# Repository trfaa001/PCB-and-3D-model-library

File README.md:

# PCB and 3D model library
A portfolio of small PCB designs, schematics and 3D models that are too minor to justify having their own repository.

Click on any hyperlink to view images, renders and CAD files for specified item.

### PCB / Electrical Projects
- [DIP-8 breakout board](/PCB/Kicad/DIP8%20breakout/README.md) (soldering unfinished)
- [OV-imponator power circuit](/PCB/Kicad/imponatorPower/README.md)

### 3D design/printing projects
#### Related to sim racing
- [Motor table clamp](/3D/Fusion_360/Sim_racing_table_clamp/README.md)
- [Small monitor mount](/3D/Fusion_360/Small_screen_mount/README.md)
- [Motor shaft attachment for QR](/3D/Fusion_360/Motor_shaft_to_6_hole_pattern/README.md)

## Folder structure
- "/PCB/" - PCB project files, schematics
- "/3D/" - CAD files, renders

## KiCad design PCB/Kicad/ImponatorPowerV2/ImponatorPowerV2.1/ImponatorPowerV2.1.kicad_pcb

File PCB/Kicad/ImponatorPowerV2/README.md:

# OV-imponator power circuit

<!-- Project description -->
A small circuit able to charge two AA Li-Ion and Li-Po batteries with USB PD and deliver 5V power to an external device. From the previous designed I have added a LED matrix, 4 buttons, 1 microphone, 4 addresable LEDs and a sliding POT.meter connected to a Silicon Labs microcontroller.

I routed a 4 layer and a 6 layer PCB for this design, because the price for a 6 layer design was cheaper when I checked the price of ordering a 4 layer pcb with vias in pads.

## images
### PCB design
#### 4 layer PCB

#### 6 layer PCB

## Physical image

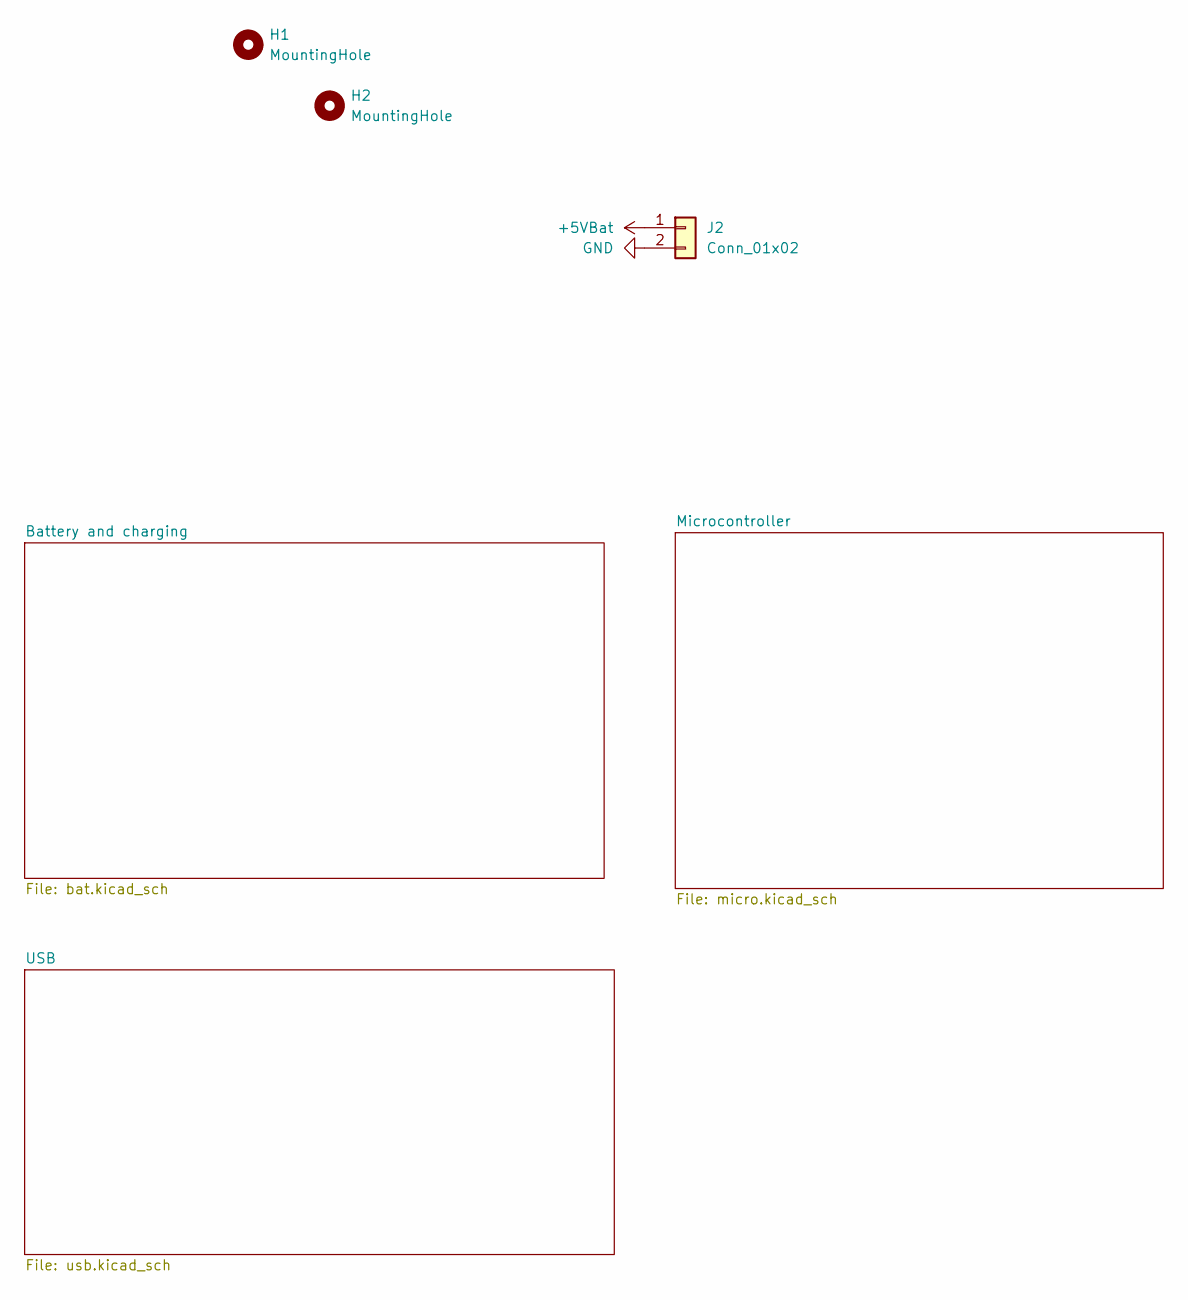
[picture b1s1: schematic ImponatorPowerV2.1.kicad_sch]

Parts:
H1, H2: MountingHole; MountingHole_2.2mm_M2
J2: Conn_01x02; JST_XH_S2B-XH-A_1x02_P2.50mm_Horizontal

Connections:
+5VBat: J2.1; also elsewhere on the board
GND: J2.2; also elsewhere on the board

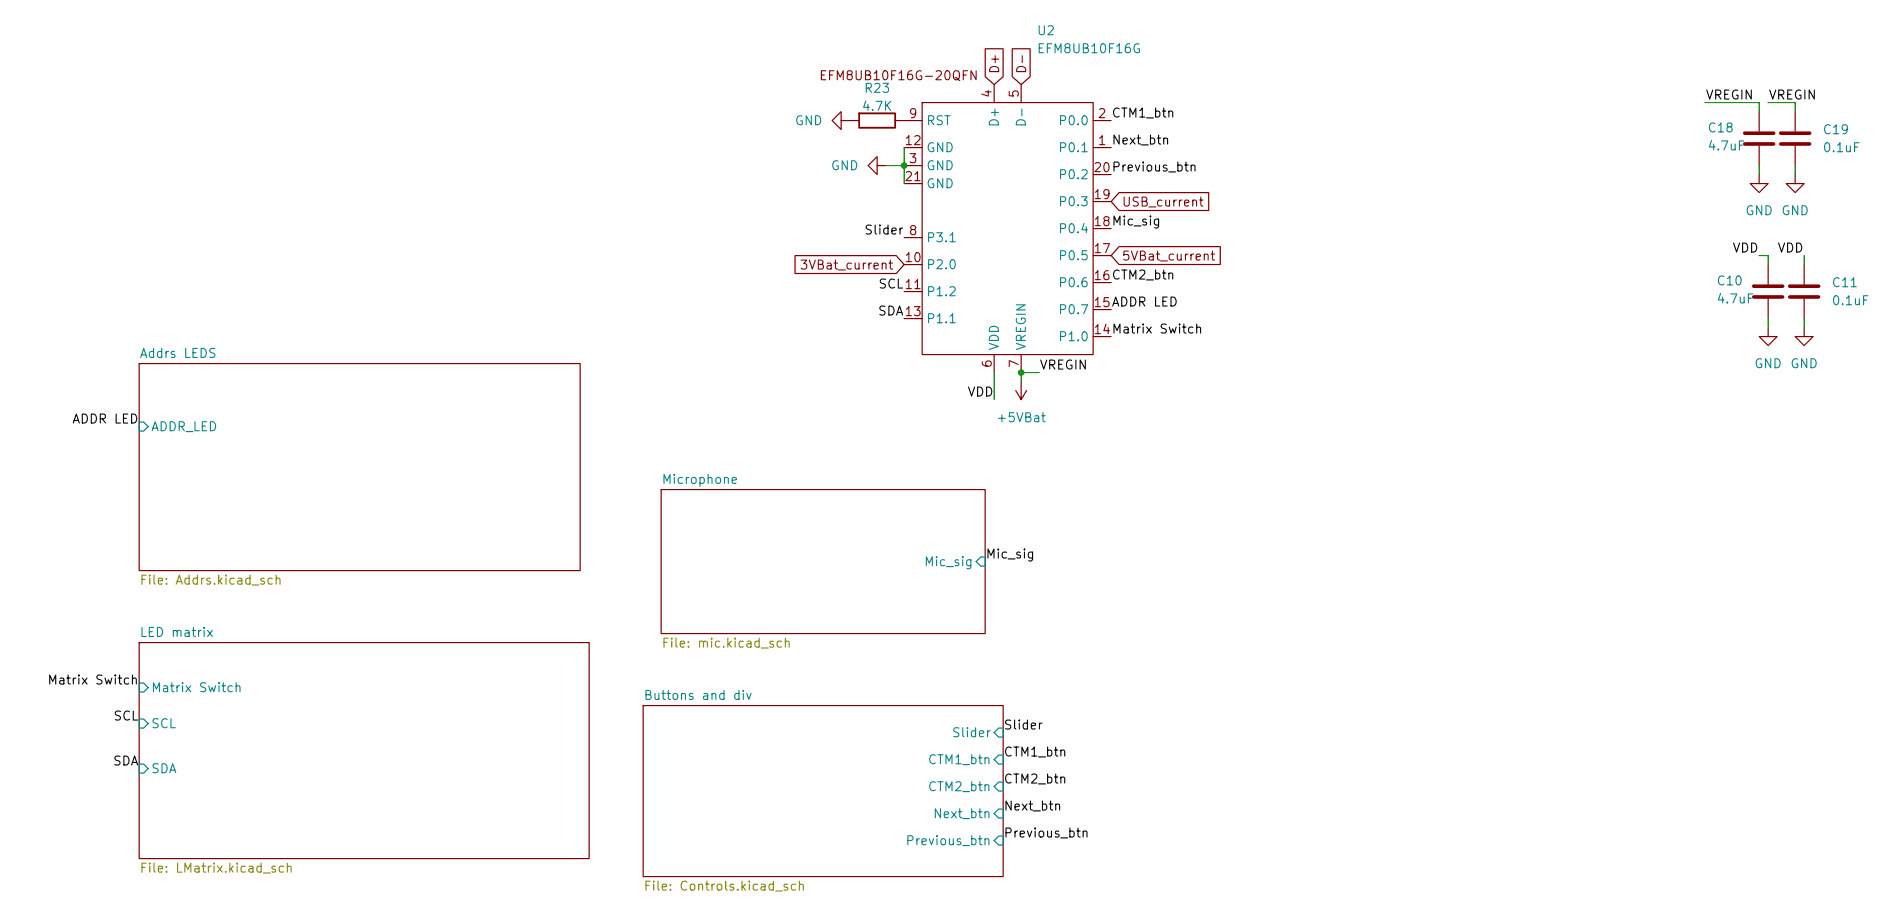
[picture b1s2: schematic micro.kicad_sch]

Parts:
C10, C18: 4.7uF; C_0805_2012Metric
C11, C19: 0.1uF; C_0805_2012Metric
R23: 4.7K; R_0603_1608Metric
U2: EFM8UB10F16G; QFN-20-1EP_3x3mm_P0.4mm_EP1.65x1.65mm

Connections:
3VBat_current: U2.10 (P2.0); also elsewhere on the board
5VBat_current: U2.17 (P0.5); also elsewhere on the board
+5VBat: C18.1, C19.1, U2.7 (VREGIN); also elsewhere on the board
/Microcontroller/ADDR LED: U2.15 (P0.7); also elsewhere on the board
/Microcontroller/CTM1_btn: U2.2 (P0.0); also elsewhere on the board
/Microcontroller/CTM2_btn: U2.16 (P0.6); also elsewhere on the board
/Microcontroller/Matrix Switch: U2.14 (P1.0); also elsewhere on the board
/Microcontroller/Mic_sig: U2.18 (P0.4); also elsewhere on the board
/Microcontroller/Next_btn: U2.1 (P0.1); also elsewhere on the board
/Microcontroller/Previous_btn: U2.20 (P0.2); also elsewhere on the board
/Microcontroller/SCL: U2.11 (P1.2); also elsewhere on the board
/Microcontroller/SDA: U2.13 (P1.1); also elsewhere on the board
/Microcontroller/Slider: U2.8 (P3.1); also elsewhere on the board
/Microcontroller/VDD: C10.1, C11.1, U2.6 (VDD)
D+: U2.4 (D+); also elsewhere on the board
D-: U2.5 (D-); also elsewhere on the board
GND: C10.2, C11.2, C18.2, C19.2, R23.2, U2.3 (GND), U2.12 (GND), U2.21 (GND); also elsewhere on the board
unnamed: R23.1, U2.9 (RST)
USB_current: U2.19 (P0.3); also elsewhere on the board

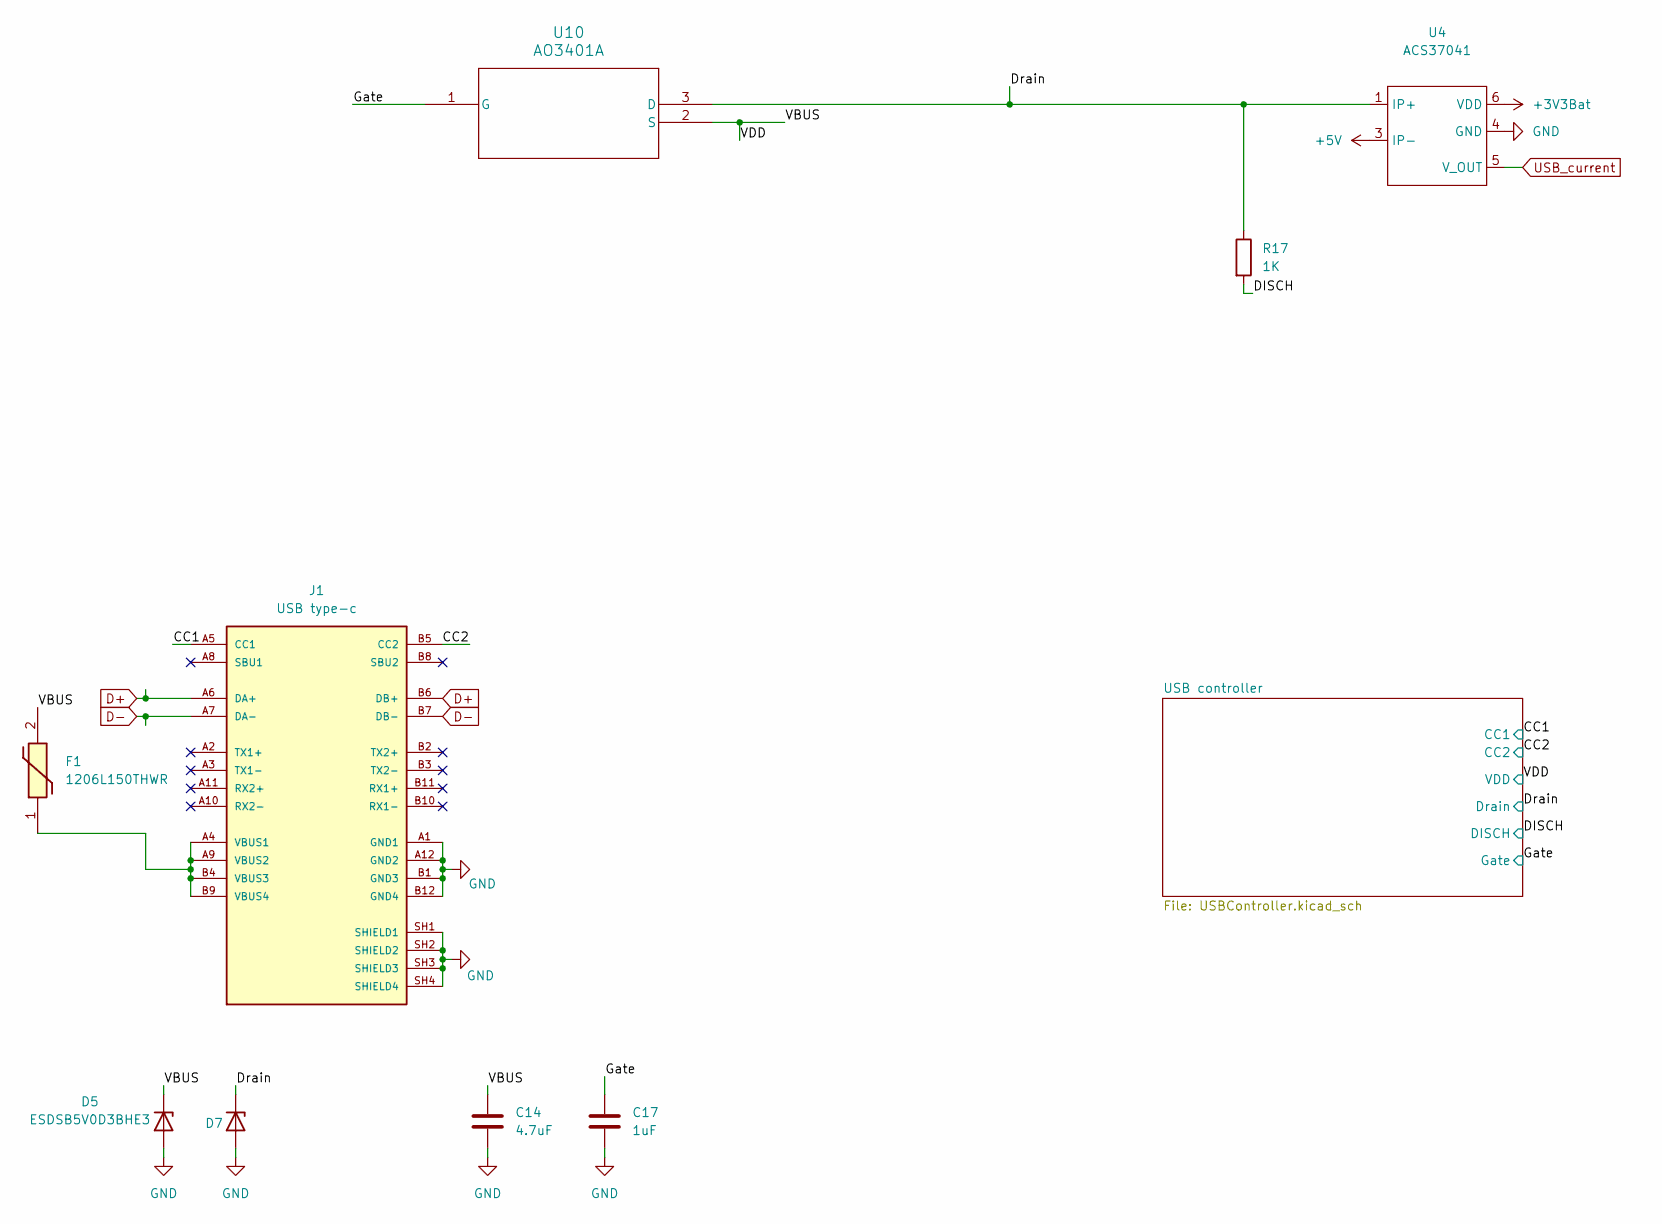
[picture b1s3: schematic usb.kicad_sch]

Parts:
C14: 4.7uF; C_0603_1608Metric
C17: 1uF; C_0603_1608Metric
D5, D7: ESDSB5V0D3BHE3; D_SOD-323
F1: 1206L150THWR; FUSC3216X100N; Manufacturer_Part_Number 1206L150THWR
J1: USB type-c; MOLEX_2024100002; PARTREV F1
R17: 1K; R_0603_1608Metric
U4: ACS37041; ACS37041KLHBLT-010B5
U10: AO3401A; SOT-23-3L_AOS

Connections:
+3V3Bat: U4.6 (VDD); also elsewhere on the board
+5V: U4.3 (IP-); also elsewhere on the board
/USB/CC1: J1.A5 (CC1); also elsewhere on the board
/USB/CC2: J1.B5 (CC2); also elsewhere on the board
/USB/DISCH: R17.2; also elsewhere on the board
/USB/Drain: D7.1 (K), R17.1, U4.1 (IP+), U10.3 (D); also elsewhere on the board
/USB/Gate: C17.1, U10.1 (G); also elsewhere on the board
/USB/VBUS: C14.1, D5.1 (K), F1.2, U10.2 (S); also elsewhere on the board
D+: J1.A6 (DA+), J1.B6 (DB+); also elsewhere on the board
D-: J1.A7 (DA-), J1.B7 (DB-); also elsewhere on the board
GND: C14.2, C17.2, D5.2 (A), D7.2 (A), J1.A1 (GND1), J1.A12 (GND2), J1.B1 (GND3), J1.B12 (GND4), J1.SH1 (SHIELD1), J1.SH2 (SHIELD2), J1.SH3 (SHIELD3), J1.SH4 (SHIELD4), U4.4 (GND); also elsewhere on the board
unnamed: F1.1, J1.A4 (VBUS1), J1.A9 (VBUS2), J1.B4 (VBUS3), J1.B9 (VBUS4)
USB_current: U4.5 (V_OUT); also elsewhere on the board

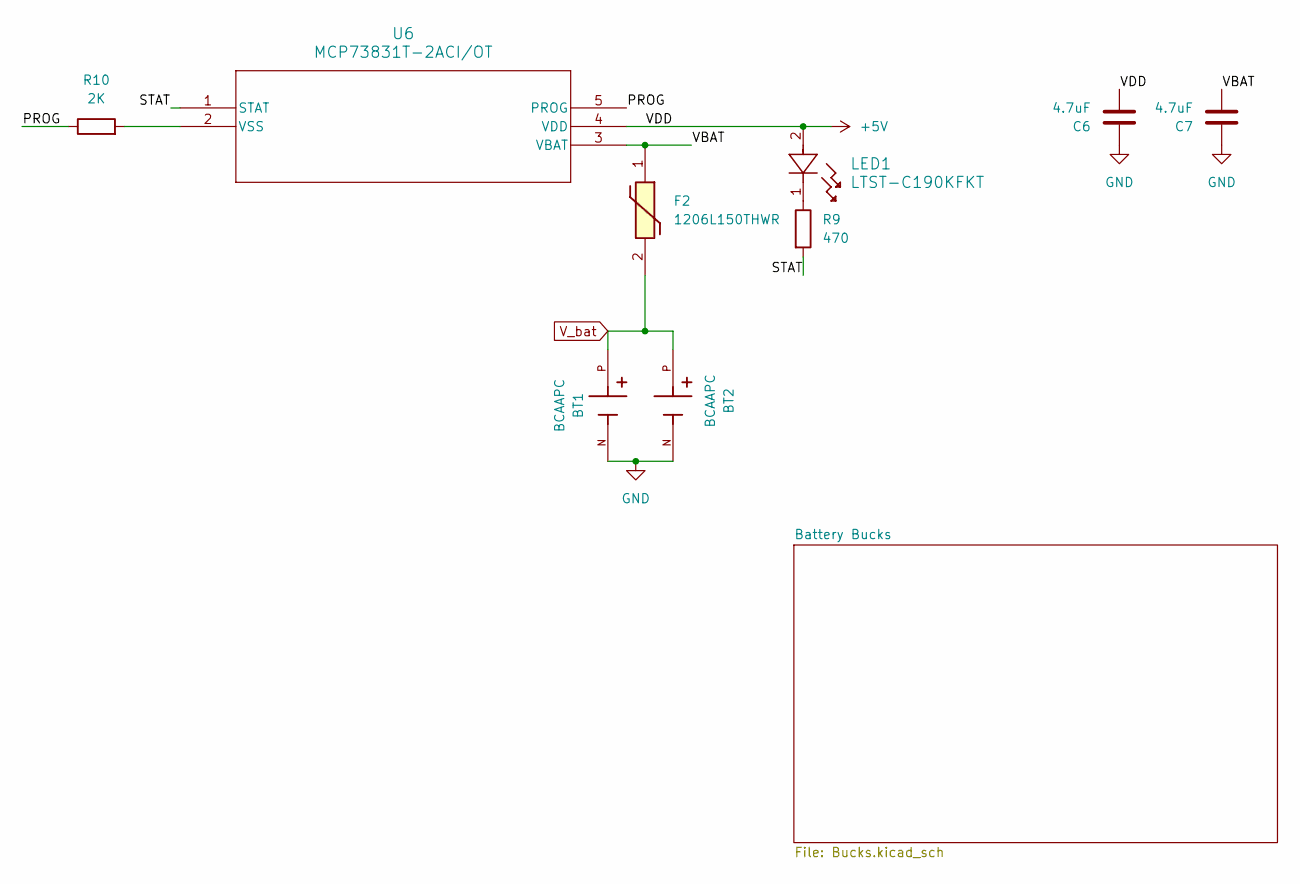
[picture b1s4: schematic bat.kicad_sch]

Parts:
BT1, BT2: BCAAPC; BAT_BCAAPC; PARTREV B
C6, C7: 4.7uF; C_0603_1608Metric
F2: 1206L150THWR; FUSC3216X100N; Manufacturer_Part_Number 1206L150THWR
LED1: LTST-C190KFKT; LED_LSTS-C190_LTO
R9: 470; R_0603_1608Metric
R10: 2K; R_0603_1608Metric
U6: MCP73831T-2ACI/OT; SOT-23-5

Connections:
+5V: C6.2, LED1.2, U6.4 (VDD); also elsewhere on the board
/Battery and charging/PROG: R10.1, U6.5 (PROG)
/Battery and charging/STAT: R9.2, U6.1 (STAT)
/Battery and charging/VBAT: C7.2, F2.1, U6.3 (VBAT)
GND: BT1.N, BT2.N, C6.1, C7.1; also elsewhere on the board
unnamed: LED1.1, R9.1
unnamed: R10.2, U6.2 (VSS)
V_bat: BT1.P, BT2.P, F2.2; also elsewhere on the board

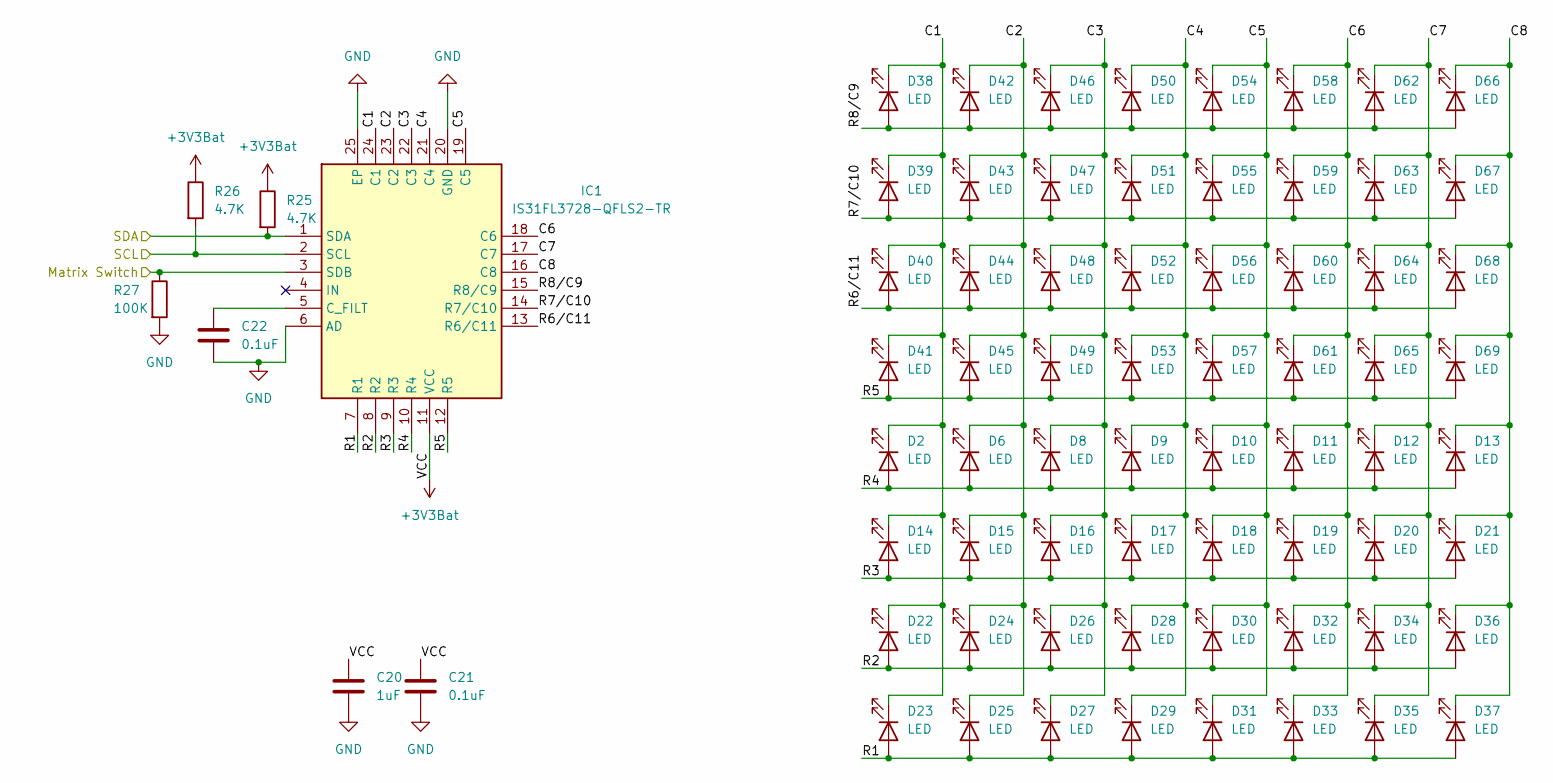
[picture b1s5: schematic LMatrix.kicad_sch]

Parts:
C20: 1uF; C_0805_2012Metric
C21: 0.1uF; C_0805_2012Metric
C22: 0.1uF; C_0603_1608Metric
D2, D6, D8, D9, D10, D11, D12, D13, D14, D15, D16, D17, D18, D19, D20, D21, D22, D23, D24, D25, D26, D27, D28, D29, D30, D31, D32, D33, D34, D35, D36, D37, D38, D39, D40, D41, D42, D43, D44, D45, D46, D47, D48, D49, D50, D51, D52, D53, D54, D55, D56, D57, D58, D59, D60, D61, D62, D63, D64, D65, D66, D67, D68, D69: LED; LED_Matrix
IC1: IS31FL3728-QFLS2-TR; QFN-24-1EP_4x4mm_P0.5mm_EP2.5x2.5mm; Manufacturer_Part_Number IS31FL3728-QFLS2-TR; Mouser Part Number 870-IS31FL3728QFLS2R
R25, R26: 4.7K; R_0603_1608Metric
R27: 100K; R_0603_1608Metric

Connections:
+3V3Bat: C20.1, C21.1, IC1.11 (VCC), R25.1, R26.1; also elsewhere on the board
/Microcontroller/LED matrix/C1: D2.1 (K), D14.1 (K), D22.1 (K), D23.1 (K), D38.1 (K), D39.1 (K), D40.1 (K), D41.1 (K), IC1.24 (C1)
/Microcontroller/LED matrix/C2: D6.1 (K), D15.1 (K), D24.1 (K), D25.1 (K), D42.1 (K), D43.1 (K), D44.1 (K), D45.1 (K), IC1.23 (C2)
/Microcontroller/LED matrix/C3: D8.1 (K), D16.1 (K), D26.1 (K), D27.1 (K), D46.1 (K), D47.1 (K), D48.1 (K), D49.1 (K), IC1.22 (C3)
/Microcontroller/LED matrix/C4: D9.1 (K), D17.1 (K), D28.1 (K), D29.1 (K), D50.1 (K), D51.1 (K), D52.1 (K), D53.1 (K), IC1.21 (C4)
/Microcontroller/LED matrix/C5: D10.1 (K), D18.1 (K), D30.1 (K), D31.1 (K), D54.1 (K), D55.1 (K), D56.1 (K), D57.1 (K), IC1.19 (C5)
/Microcontroller/LED matrix/C6: D11.1 (K), D19.1 (K), D32.1 (K), D33.1 (K), D58.1 (K), D59.1 (K), D60.1 (K), D61.1 (K), IC1.18 (C6)
/Microcontroller/LED matrix/C7: D12.1 (K), D20.1 (K), D34.1 (K), D35.1 (K), D62.1 (K), D63.1 (K), D64.1 (K), D65.1 (K), IC1.17 (C7)
/Microcontroller/LED matrix/C8: D13.1 (K), D21.1 (K), D36.1 (K), D37.1 (K), D66.1 (K), D67.1 (K), D68.1 (K), D69.1 (K), IC1.16 (C8)
/Microcontroller/LED matrix/R1: D23.2 (A), D25.2 (A), D27.2 (A), D29.2 (A), D31.2 (A), D33.2 (A), D35.2 (A), D37.2 (A), IC1.7 (R1)
/Microcontroller/LED matrix/R2: D22.2 (A), D24.2 (A), D26.2 (A), D28.2 (A), D30.2 (A), D32.2 (A), D34.2 (A), D36.2 (A), IC1.8 (R2)
/Microcontroller/LED matrix/R3: D14.2 (A), D15.2 (A), D16.2 (A), D17.2 (A), D18.2 (A), D19.2 (A), D20.2 (A), D21.2 (A), IC1.9 (R3)
/Microcontroller/LED matrix/R4: D2.2 (A), D6.2 (A), D8.2 (A), D9.2 (A), D10.2 (A), D11.2 (A), D12.2 (A), D13.2 (A), IC1.10 (R4)
/Microcontroller/LED matrix/R5: D41.2 (A), D45.2 (A), D49.2 (A), D53.2 (A), D57.2 (A), D61.2 (A), D65.2 (A), D69.2 (A), IC1.12 (R5)
/Microcontroller/LED matrix/R6/C11: D40.2 (A), D44.2 (A), D48.2 (A), D52.2 (A), D56.2 (A), D60.2 (A), D64.2 (A), D68.2 (A), IC1.13 (R6/C11)
/Microcontroller/LED matrix/R7/C10: D39.2 (A), D43.2 (A), D47.2 (A), D51.2 (A), D55.2 (A), D59.2 (A), D63.2 (A), D67.2 (A), IC1.14 (R7/C10)
/Microcontroller/LED matrix/R8/C9: D38.2 (A), D42.2 (A), D46.2 (A), D50.2 (A), D54.2 (A), D58.2 (A), D62.2 (A), D66.2 (A), IC1.15 (R8/C9)
/Microcontroller/Matrix Switch: IC1.3 (SDB), R27.1; also elsewhere on the board
/Microcontroller/SCL: IC1.2 (SCL), R26.2; also elsewhere on the board
/Microcontroller/SDA: IC1.1 (SDA), R25.2; also elsewhere on the board
GND: C20.2, C21.2, C22.2, IC1.6 (AD), IC1.20 (GND), IC1.25 (EP), R27.2; also elsewhere on the board
unnamed: C22.1, IC1.5 (C_FILT)

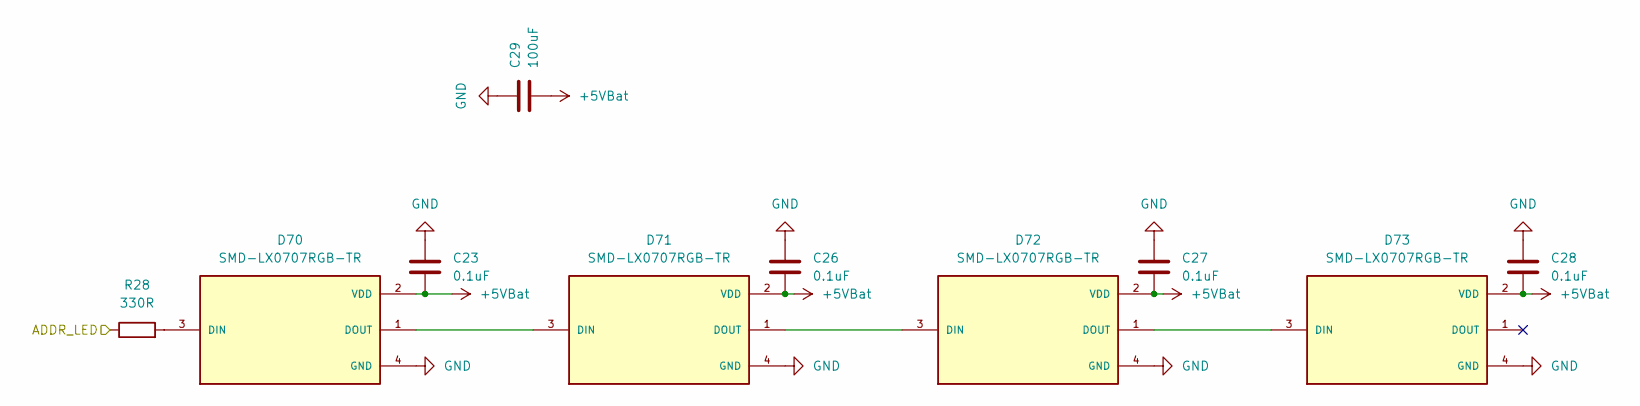
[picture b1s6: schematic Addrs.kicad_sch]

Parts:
C23, C26, C27, C28: 0.1uF; C_0805_2012Metric
C29: 100uF; C_0805_2012Metric
D70, D71, D72, D73: SMD-LX0707RGB-TR; LED_SMD-LX0707RGB-TR; PARTREV D
R28: 330R; R_0805_2012Metric

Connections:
+5VBat: C23.2, C26.2, C27.2, C28.2, C29.2, D70.2 (VDD), D71.2 (VDD), D72.2 (VDD), D73.2 (VDD); also elsewhere on the board
/Microcontroller/ADDR LED: R28.1; also elsewhere on the board
GND: C23.1, C26.1, C27.1, C28.1, C29.1, D70.4 (GND), D71.4 (GND), D72.4 (GND), D73.4 (GND); also elsewhere on the board
unnamed: D70.3 (DIN), R28.2
unnamed: D70.1 (DOUT), D71.3 (DIN)
unnamed: D71.1 (DOUT), D72.3 (DIN)
unnamed: D72.1 (DOUT), D73.3 (DIN)

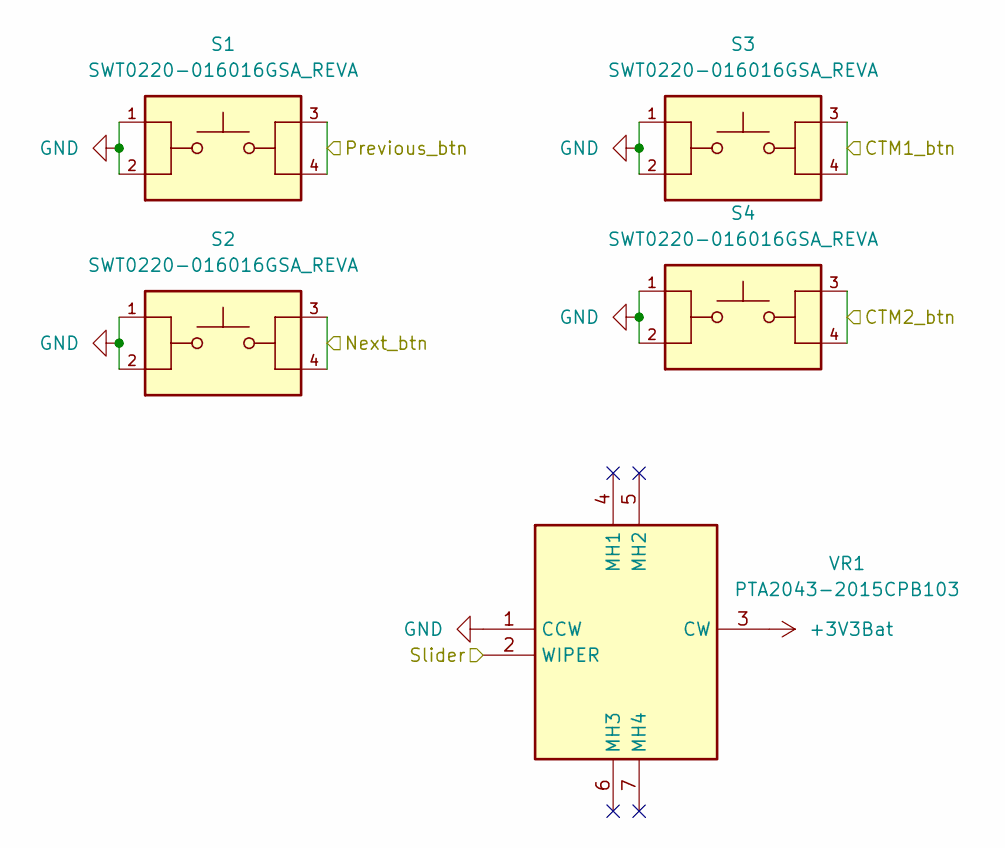
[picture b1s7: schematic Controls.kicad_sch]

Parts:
S1, S2, S3, S4: SWT0220-016016GSA_REVA; SW_SWT0220-016016GSA_REVA; PARTREV A
VR1: PTA2043-2015CPB103; PTA20432015CPB103; Mouser Part Number 652-PTA20432015CPB10

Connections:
+3V3Bat: VR1.3 (CW); also elsewhere on the board
/Microcontroller/CTM1_btn: S3.3, S3.4; also elsewhere on the board
/Microcontroller/CTM2_btn: S4.3, S4.4; also elsewhere on the board
/Microcontroller/Next_btn: S2.3, S2.4; also elsewhere on the board
/Microcontroller/Previous_btn: S1.3, S1.4; also elsewhere on the board
/Microcontroller/Slider: VR1.2 (WIPER); also elsewhere on the board
GND: S1.1, S1.2, S2.1, S2.2, S3.1, S3.2, S4.1, S4.2, VR1.1 (CCW); also elsewhere on the board

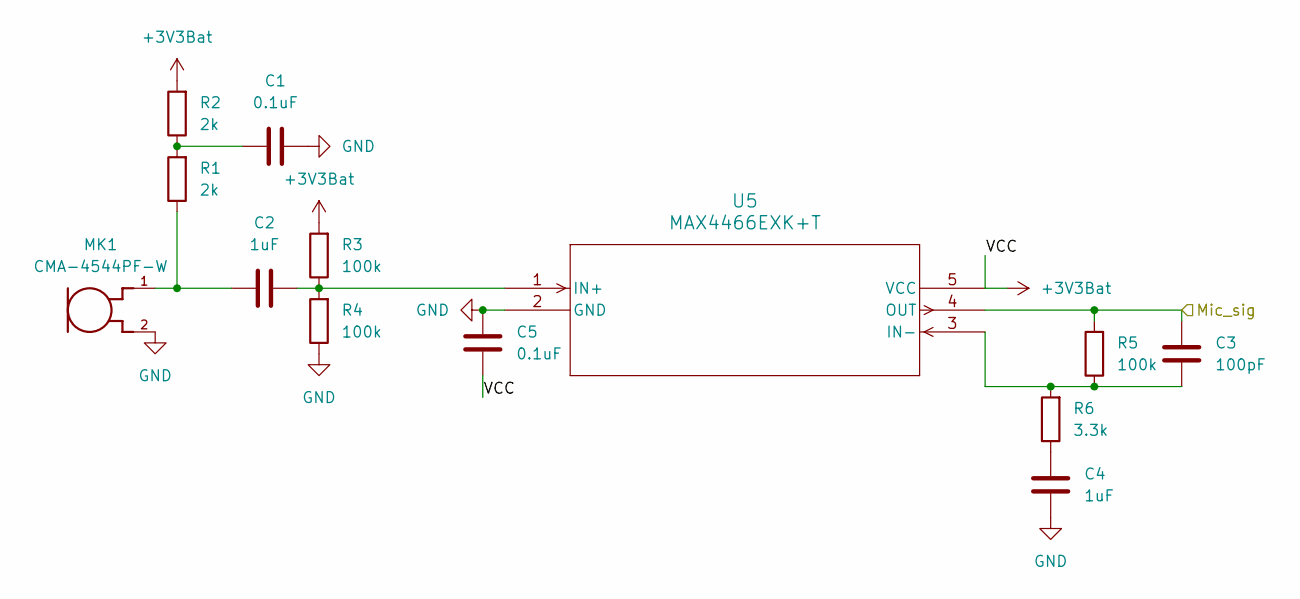
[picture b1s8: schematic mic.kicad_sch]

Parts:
C1, C5: 0.1uF; C_0603_1608Metric
C2, C4: 1uF; C_0603_1608Metric
C3: 100pF; C_0603_1608Metric
MK1: CMA-4544PF-W; MIC_CMA-4544PF-W
R1, R2: 2k; R_0603_1608Metric
R3, R4, R5: 100k; R_0603_1608Metric
R6: 3.3k; R_0603_1608Metric
U5: MAX4466EXK+T; 21-0076E_MXM

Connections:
+3V3Bat: C5.2, R2.2, R3.2, U5.5 (VCC); also elsewhere on the board
/Microcontroller/Mic_sig: C3.1, R5.2, U5.4 (OUT); also elsewhere on the board
GND: C1.2, C4.2, C5.1, MK1.2, R4.1, U5.2 (GND); also elsewhere on the board
unnamed: C1.1, R1.2, R2.1
unnamed: C2.1, MK1.1, R1.1
unnamed: C4.1, R6.1
unnamed: C2.2, R3.1, R4.2, U5.1 (IN+)
unnamed: C3.2, R5.1, R6.2, U5.3 (IN-)

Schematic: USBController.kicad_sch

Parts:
C12, C15, C16: 1uF; C_0603_1608Metric
C13: 100nF; C_0603_1608Metric
D4: BZT52B5V1; D_SOD-123
J3: Conn_01x04_Pin; PinHeader_1x04_P2.54mm_Vertical
R7: 470R; R_0603_1608Metric
R8: 1K; R_0603_1608Metric
R14: 22K; R_0603_1608Metric
R15, R18, R21, R22: 100K; R_0603_1608Metric
R16: 10K; R_0603_1608Metric
R19: 100R; R_0603_1608Metric
R20: 22R; R_0603_1608Metric
U1: STUSB4500QTR; QFN24EP_4X4_STM

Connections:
+2V7: C16.1, R20.1, R21.1, U1.23 (VREG_2V7)
/USB/CC1: U1.1 (CC1DB), U1.2 (CC1); also elsewhere on the board
/USB/CC2: U1.4 (CC2), U1.5 (CC2DB); also elsewhere on the board
/USB/DISCH: U1.9 (DISCH); also elsewhere on the board
/USB/Drain: C13.1; also elsewhere on the board
/USB/Gate: R14.2, R15.1, R19.1; also elsewhere on the board
/USB/USB controller/VS: R8.1, U1.18 (VBUS_VS_DISCH)
/USB/USB controller/Vbus_en_SNK: R14.1, U1.16 (VBUS_EN_SNK)
/USB/VBUS: D4.2 (A), J3.1, R7.2, R15.2, U1.24 (VDD); also elsewhere on the board
GND: C12.1, C15.2, C16.2, J3.4, R16.2, R18.2, R22.2, U1.10 (GND), U1.22 (VSYS), U1.25 (EP); also elsewhere on the board
unnamed: C13.2, R19.2
unnamed: C12.2, D4.1 (K), R7.1, R8.2
unnamed: J3.2, U1.7 (SCL)
unnamed: J3.3, U1.8 (SDA)
unnamed: R18.1, R20.2, U1.12 (ADDR0)
unnamed: R21.2, R22.1, U1.13 (ADDR1)
unnamed: R16.1, U1.6 (RESET)
unnamed: C15.1, U1.21 (VREG_1V2)

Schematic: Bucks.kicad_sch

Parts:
C8, C24: 4.7uF; C_0805_2012Metric
C9, C25: 22uF; C_0805_2012Metric
L1, L2: 1.0uH; L_0805_2012Metric
Q1, Q2: AO3400A; UMW A03400A
R11: 604K; R_0603_1608Metric
R12, R31: 82K; R_0603_1608Metric
R13, R29: 499K; R_0603_1608Metric
R30: 369K; R_0603_1608Metric
U3, U7: TPS62A01DRLR; SOT-666
U8, U11: ACS37041; ACS37041KLHBLT-010B5

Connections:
3VBat_current: U11.5 (V_OUT); also elsewhere on the board
5VBat_current: U8.5 (V_OUT); also elsewhere on the board
+3.3V: U8.6 (VDD), U11.6 (VDD)
+3V3Bat: U11.3 (IP-); also elsewhere on the board
+5VBat: U8.3 (IP-); also elsewhere on the board
/Battery and charging/Battery Bucks/PG: Q1.2 (G), R13.2, U3.6 (PG)
/Battery and charging/Battery Bucks/PG2: Q2.2 (G), R29.2, U7.6 (PG)
/Battery and charging/Battery Bucks/SW: L1.1, U3.2 (SW)
/Battery and charging/Battery Bucks/SW2: L2.1, U7.2 (SW)
GND: C8.2, C9.2, C24.2, C25.2, R12.2, R31.2, U3.1 (GND), U7.1 (GND), U8.4 (GND), U11.4 (GND); also elsewhere on the board
unnamed: C9.1, L1.2, Q1.1 (D), R11.1
unnamed: Q1.3 (S), U8.1 (IP+)
unnamed: C25.1, L2.2, Q2.1 (D), R30.1
unnamed: Q2.3 (S), U11.1 (IP+)
unnamed: R11.2, R12.1, U3.5 (FB)
unnamed: R30.2, R31.1, U7.5 (FB)
V_bat: C8.1, C24.1, R13.1, R29.1, U3.3 (VIN), U3.4 (EN), U7.3 (VIN), U7.4 (EN); also elsewhere on the board

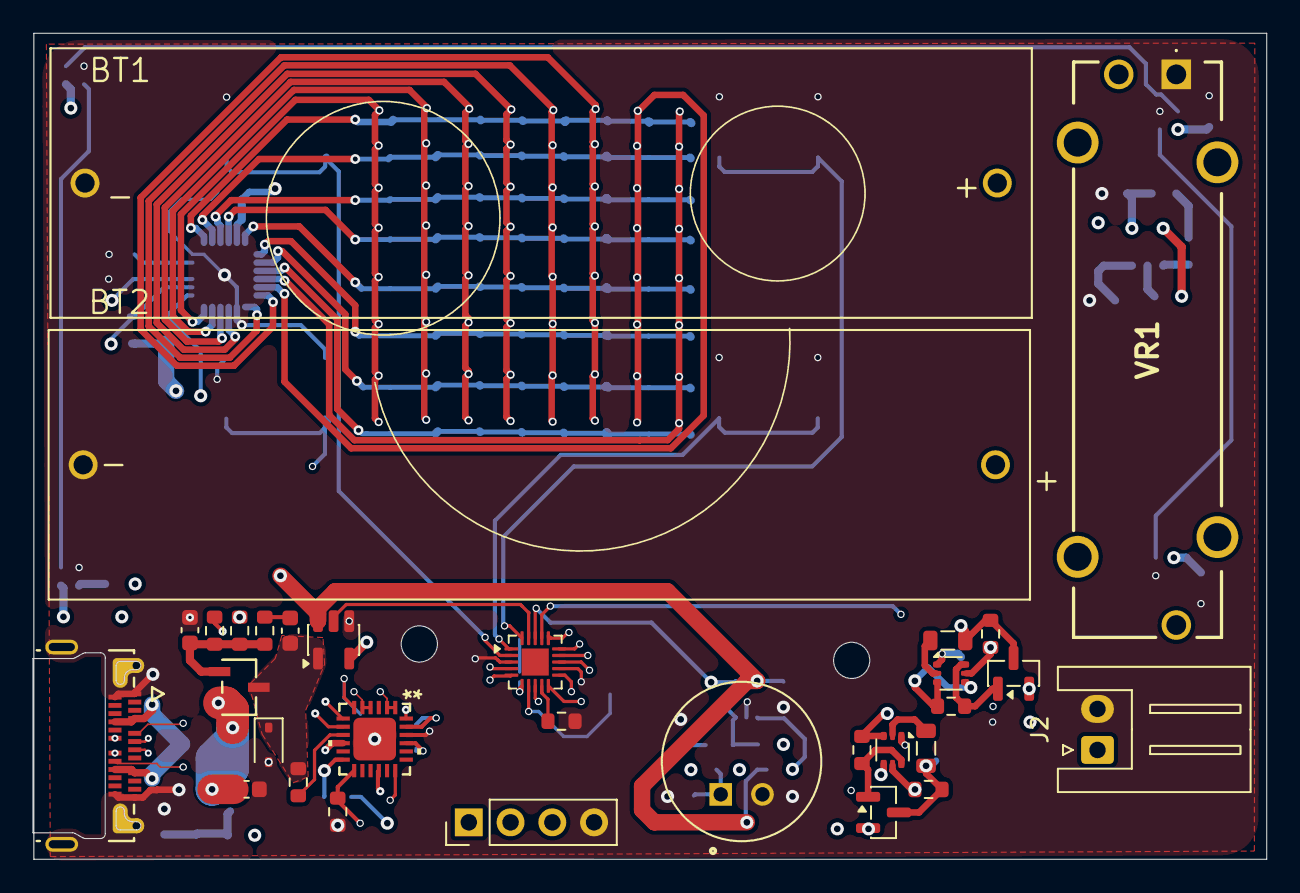
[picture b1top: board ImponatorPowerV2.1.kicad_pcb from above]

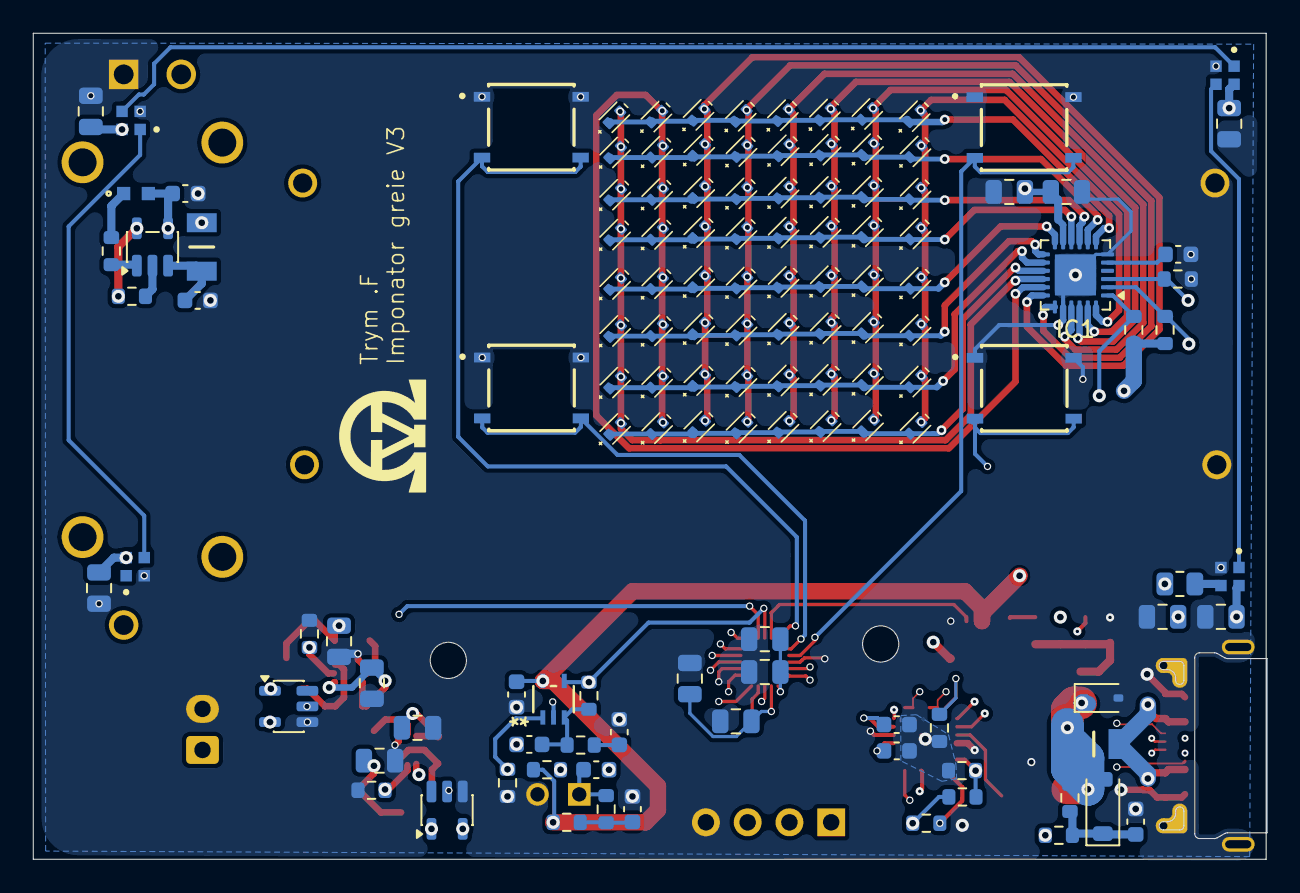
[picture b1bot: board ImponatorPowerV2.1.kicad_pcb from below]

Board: 6 copper layers, 75.0 x 50.2 mm, 161 parts (128 on the bottom side), 82 nets.

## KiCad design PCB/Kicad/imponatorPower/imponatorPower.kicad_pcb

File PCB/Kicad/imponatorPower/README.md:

# OV-imponator power circuit

<!-- Project description -->
A small circuit able to charge a AA NimH battery with USB PD and deliver 5V power to an external device. I was really dissatisfied with the cost and feature set. I will probably make a new design with more budget friendly components and more customizable features.

N.B. Some of the LEDs are misplaced in the design, and will not light up. 

## images
### PCB design

## Physical image

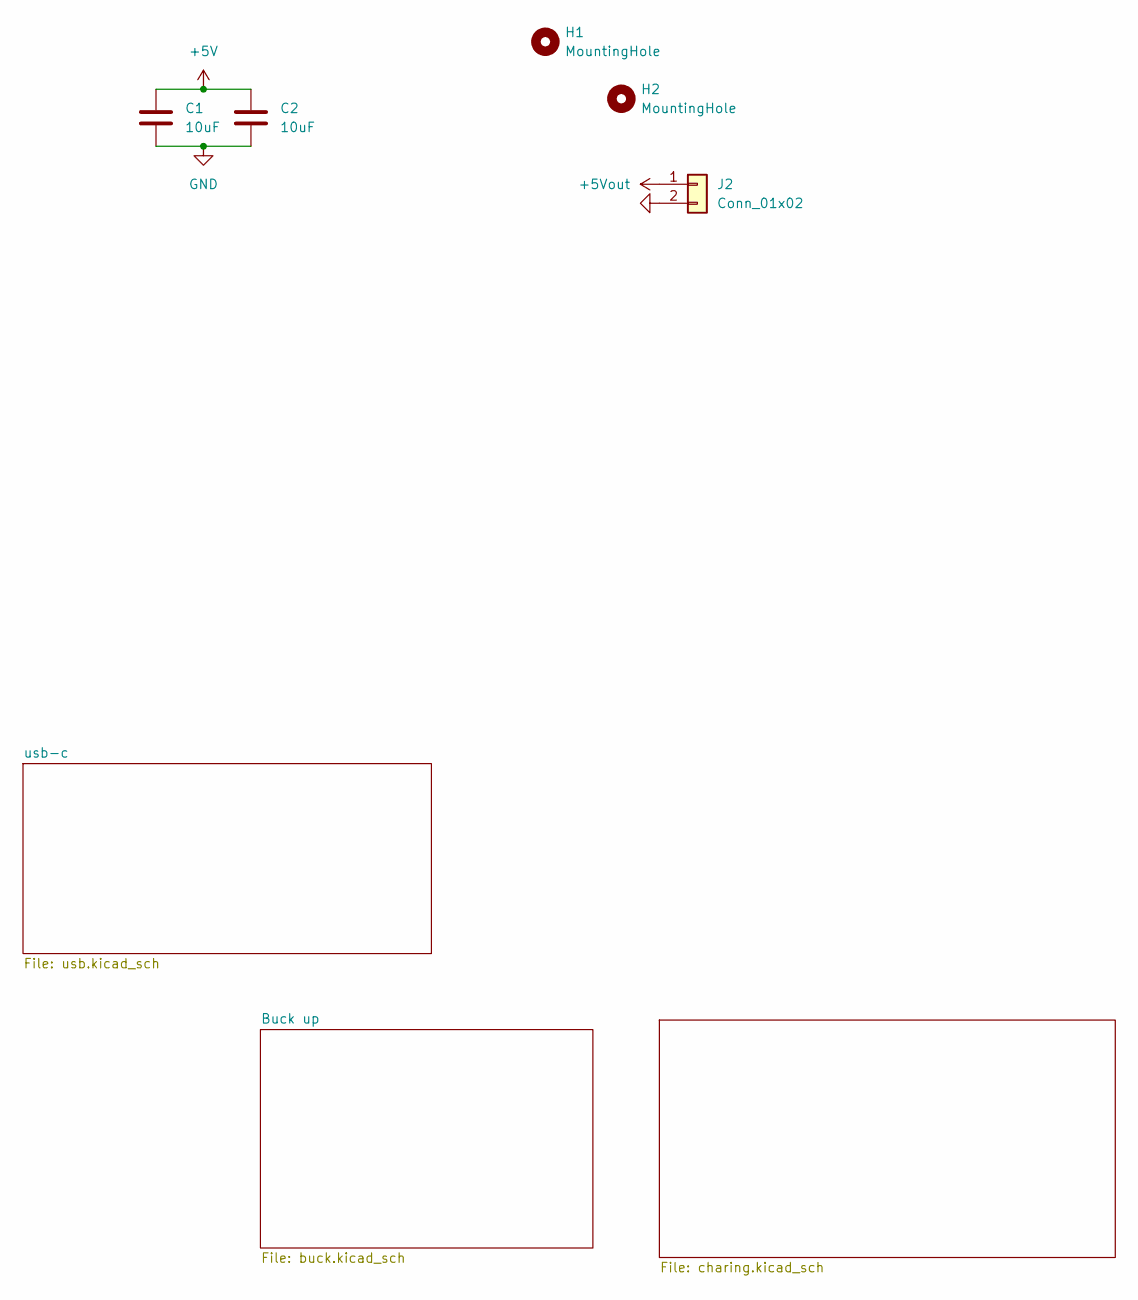
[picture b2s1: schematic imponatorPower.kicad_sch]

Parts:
C1, C2: 10uF; C_0805_2012Metric_Pad1.18x1.45mm_HandSolder
H1, H2: MountingHole; MountingHole_2.2mm_M2
J2: Conn_01x02; JST_XH_S2B-XH-A_1x02_P2.50mm_Horizontal

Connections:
+5Vout: J2.1; also elsewhere on the board
GND: C1.2, C2.2, J2.2; also elsewhere on the board
vdc_out: C1.1, C2.1; also elsewhere on the board

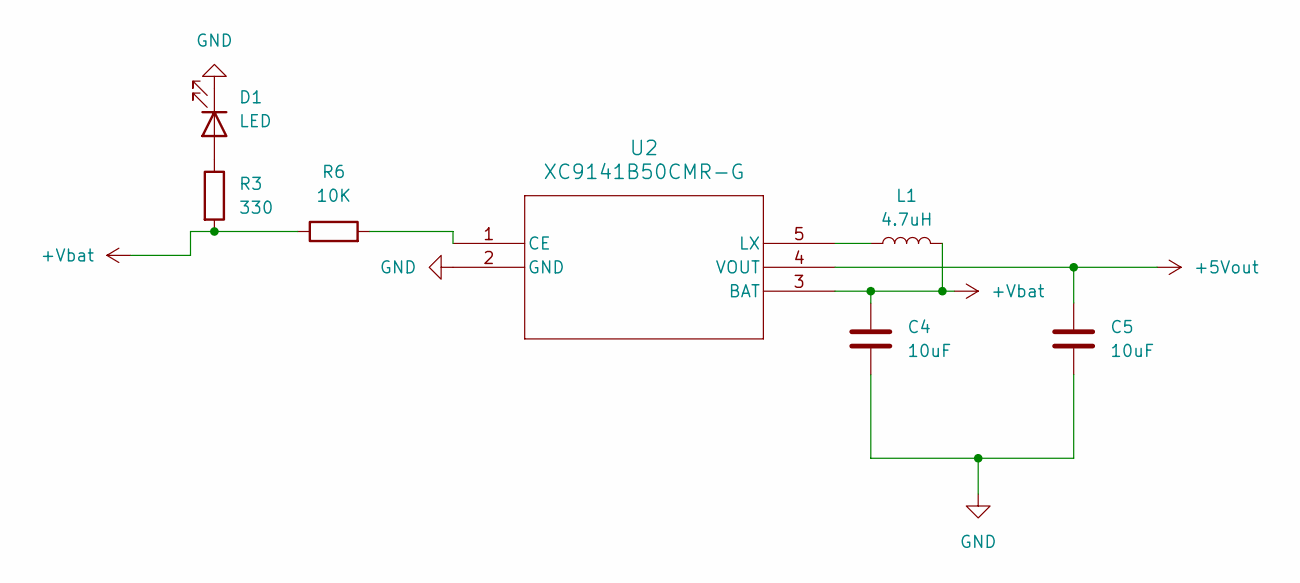
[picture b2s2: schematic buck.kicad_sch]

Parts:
C4, C5: 10uF; C_0805_2012Metric_Pad1.18x1.45mm_HandSolder
D1: LED; LED_0805_2012Metric_Pad1.15x1.40mm_HandSolder
L1: 4.7uH; IND_PCC-M0754M_PAN-L
R3: 330; R_0805_2012Metric_Pad1.20x1.40mm_HandSolder
R6: 10K; R_0805_2012Metric_Pad1.20x1.40mm_HandSolder
U2: XC9141B50CMR-G; SOT25_XC9141_TOR-L

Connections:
+5Vout: C5.1, U2.4 (VOUT); also elsewhere on the board
+Vbat: C4.1, L1.2, R3.2, R6.1, U2.3 (BAT); also elsewhere on the board
GND: C4.2, C5.2, D1.1 (K), U2.2 (GND); also elsewhere on the board
unnamed: D1.2 (A), R3.1
unnamed: R6.2, U2.1 (CE)
unnamed: L1.1, U2.5 (LX)
